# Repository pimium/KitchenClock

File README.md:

# KitchenClock
Kitchen Clock with an attiny13, oled display and two buttons.

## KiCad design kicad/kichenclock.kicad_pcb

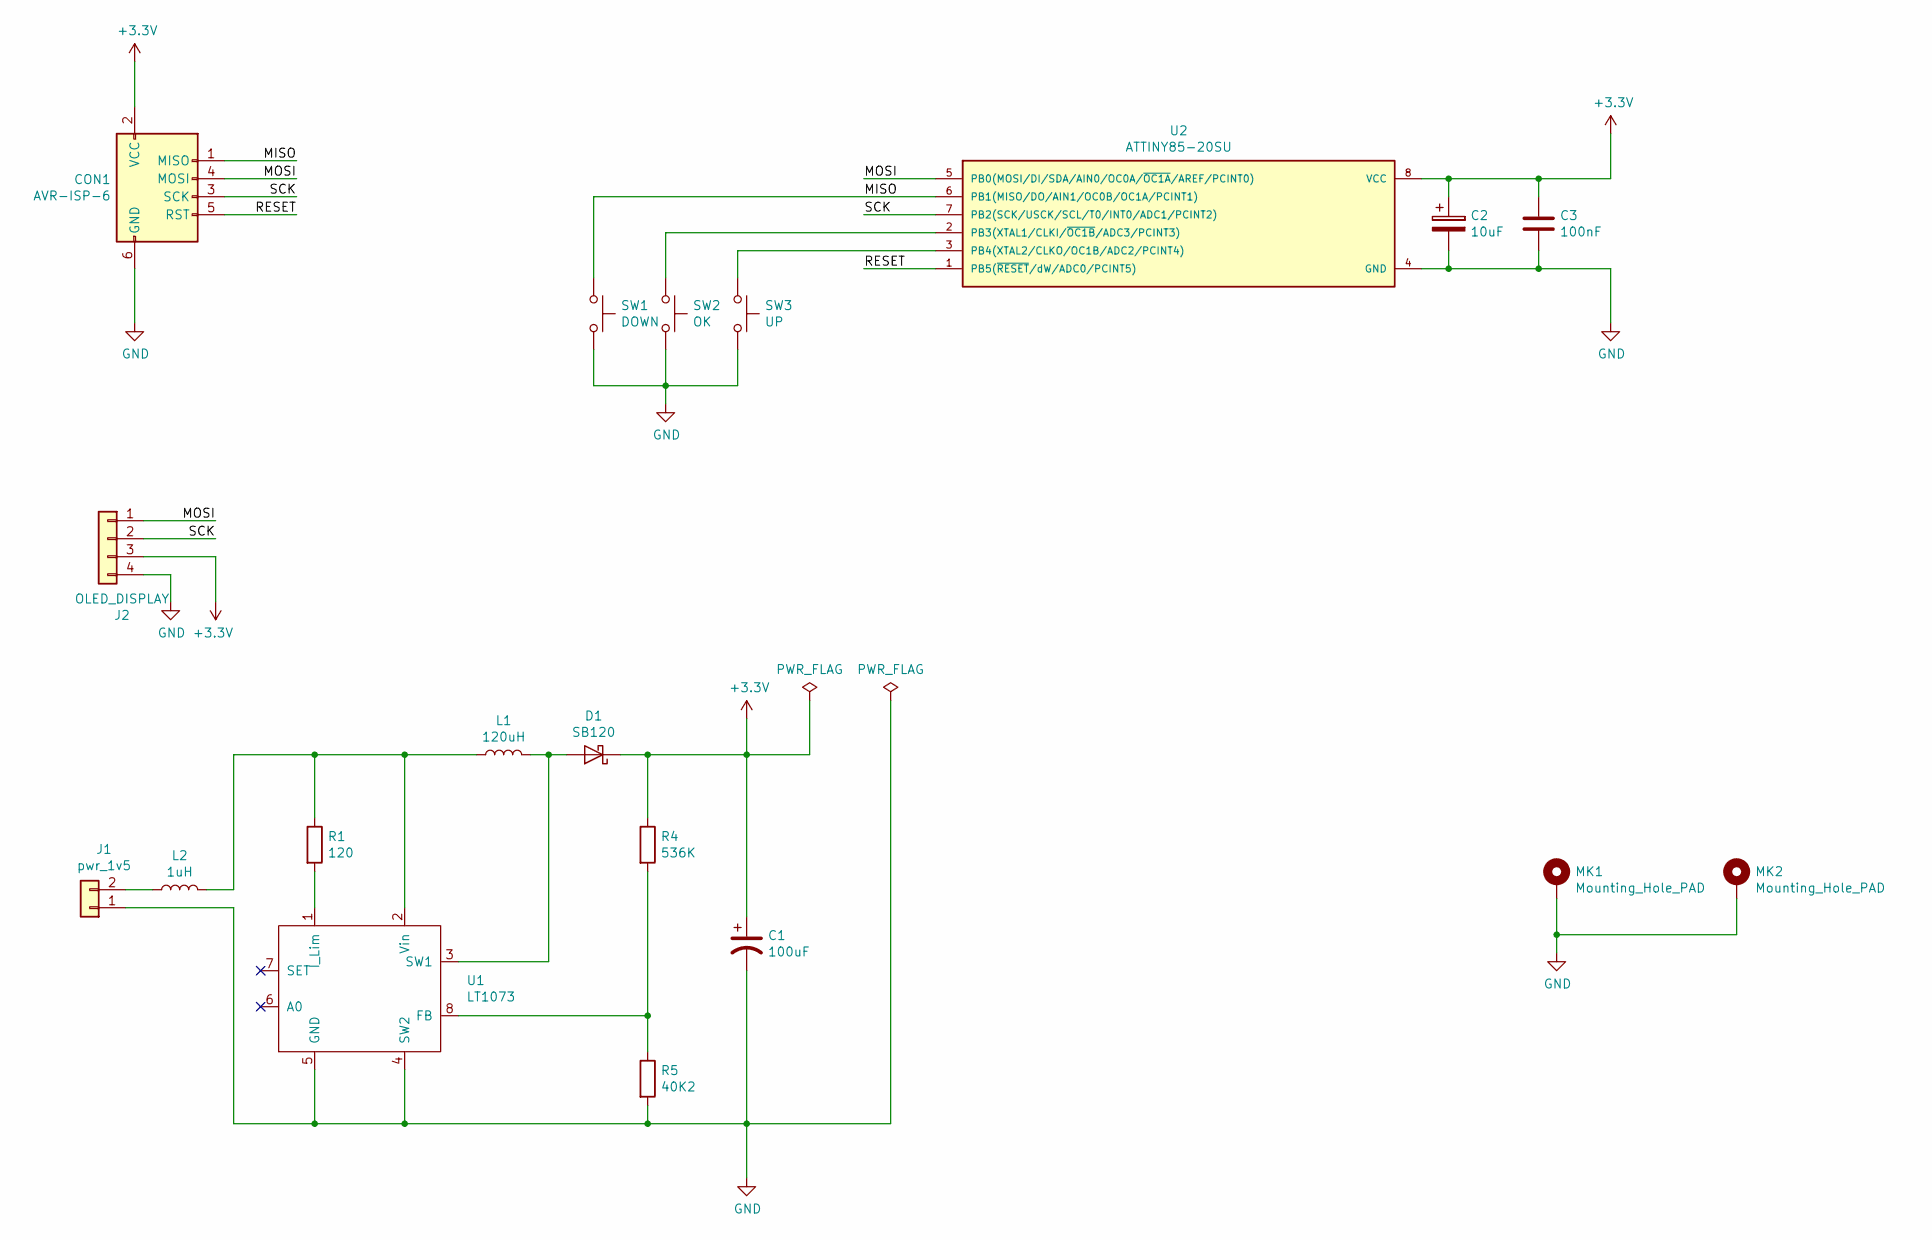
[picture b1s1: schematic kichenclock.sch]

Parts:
C1: 100uF; CP_EIA-6032-20_AVX-F_Pad2.24x2.40mm_HandSolder
C2: 10uF; CP_EIA-6032-20_AVX-F
C3: 100nF; C_0805_2012Metric_Pad1.15x1.50mm_HandSolder
CON1: AVR-ISP-6; PinSocket_2x03_P2.54mm_Vertical
D1: SB120; D_SMA_Handsoldering
J1: pwr_1v5; PinHeader_1x02_P2.54mm_Vertical
J2: OLED_DISPLAY; oled_128x32
L1: 120uH; Choke_CD75
L2: 1uH; L_0805_2012Metric_Pad1.15x1.50mm_HandSolder
MK1, MK2: Mounting_Hole_PAD; MountingHole_3mm_Pad
R1: 120; R_1206_3216Metric
R4: 536K; R_1206_3216Metric
R5: 40K2; R_1206_3216Metric
SW1: DOWN; SW_PUSH_6mm
SW2: OK; SW_PUSH_6mm
SW3: UP; SW_PUSH_6mm
U1: LT1073; SOIC-8_3.9x4.9mm_P1.27mm
U2: ATTINY85-20SU; SOIC-8_3.9x4.9mm_P1.27mm

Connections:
+3V3: C1.1, C2.1, C3.1, CON1.2 (VCC), D1.1 (K), J2.3, R4.1, U2.8 (VCC)
/MISO: CON1.1 (MISO), SW1.1, U2.6 (PB1(MISO/DO/AIN1/OC0B/OC1A/PCINT1))
/MOSI: CON1.4 (MOSI), J2.1, U2.5 (PB0(MOSI/DI/SDA/AIN0/OC0A/~OC1A~/AREF/P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)
/RESET: CON1.5 (RST), U2.1 (PB5(~RESET~/dW/ADC0/PCINT5))
/SCK: CON1.3 (SCK), J2.2, U2.7 (PB2(SCK/USCK/SCL/T0/INT0/ADC1/PCINT2))
GND: C1.2, C2.2, C3.2, CON1.6 (GND), J1.1, J2.4, MK1.1, MK2.1, R5.2, SW1.2, SW2.2, SW3.2, U1.4 (SW2), U1.5 (GND), U2.4 (GND)
unnamed: D1.2 (A), L1.2, U1.3 (SW1)
unnamed: J1.2, L2.1
unnamed: L1.1, L2.2, R1.1, U1.2 (Vin)
unnamed: R1.2, U1.1 (I_Lim)
unnamed: R4.2, R5.1, U1.8 (FB)
unnamed: SW2.1, U2.2 (PB3(XTAL1/CLKI/~OC1B~/ADC3/PCINT3))
unnamed: SW3.1, U2.3 (PB4(XTAL2/CLKO/OC1B/ADC2/PCINT4))

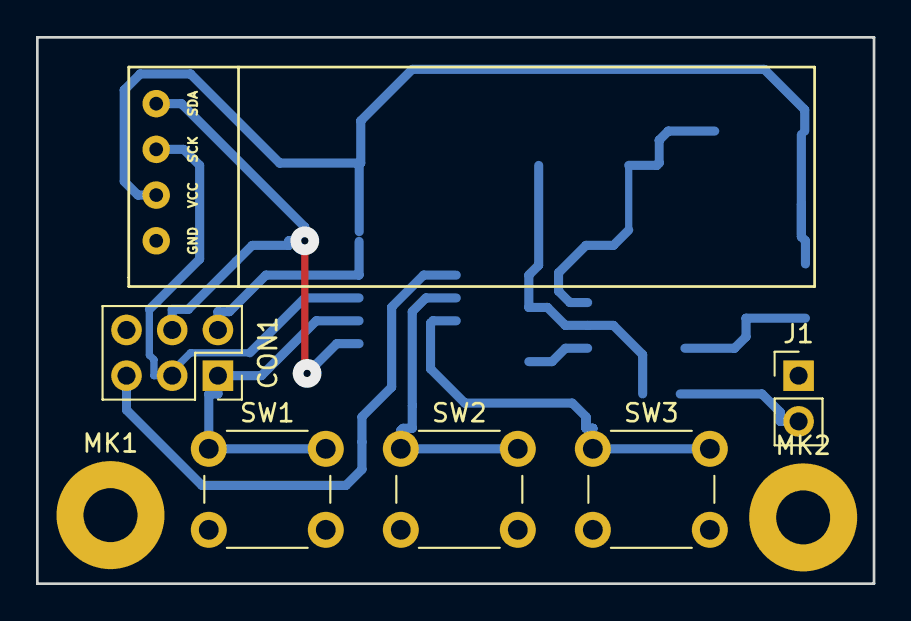
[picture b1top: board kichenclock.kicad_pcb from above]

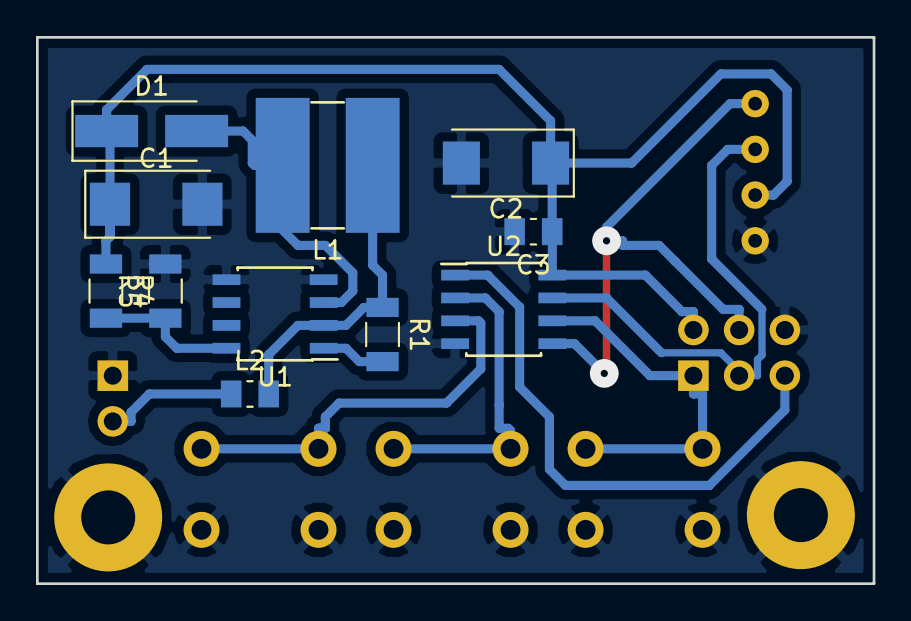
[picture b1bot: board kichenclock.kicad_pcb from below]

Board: 2 copper layers, 46.5 x 30.4 mm, 19 parts (11 on the bottom side), 13 nets.

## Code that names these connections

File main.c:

/**
 * SSD1306xLED - Drivers for SSD1306 controlled dot matrix OLED/PLED 128x64 displays
 *
 * @created: 2014-08-08
 * @author: Neven Boyanov
 *
 * This is part of the Tinusaur/SSD1306xLED project.
 *
 * Copyright (c) 2016 Neven Boyanov, Tinusaur Team. All Rights Reserved.
 * Distributed as open source software under MIT License, see LICENSE.txt file.
 * Please, as a favor, retain the link http://tinusaur.org to The Tinusaur Project.
 *
 * Source code available at: https://bitbucket.org/tinusaur/ssd1306xled
 *
 */

// ============================================================================

// #define F_CPU 1000000UL
// NOTE: The F_CPU (CPU frequency) should not be defined in the source code.
//       It should be defined in either (1) Makefile; or (2) in the IDE. 

#include <stdint.h>
#include <avr/io.h>
#include <util/delay.h>
#include <avr/interrupt.h>

//
// ~~~~~~~~~~~~~~~~~~~~~~~~~~~~~~~~~~~~~~
//                ATtiny
//               25/45/85
//              +----------+   (-)-------
//      (RST)---+ PB5  Vcc +---(+)-------
// --[OWOWOD]---+ PB3  PB2 +---[TWI/SCL]-
//           ---+ PB4  PB1 +---
// -------(-)---+ GND  PB0 +---[TWI/SDA]-
//              +----------+
//
// ~~~~~~~~~~~~~~~~~~~~~~~~~~~~~~~~~~~~~~

// -----(+)--------------->	// Vcc,	Pin 1 on SSD1306 Board
// -----(-)--------------->	// GND,	Pin 2 on SSD1306 Board
#define SSD1306_SCL        PB2    // SCL,	Pin 3 on SSD1306 Board
#define SSD1306_SDA        PB0    // SDA,	Pin 4 on SSD1306 Board

#define SSD1306_SA        0x78    // Slave address

// ----------------------------------------------------------------------------

#include "ssd1306xled.h"
//#include "print_3x7.h"
#include "print_5x7.h"
#include "print_10x14.h"
#include "num2str.h"
//#include "cpufreq.h"

// ----------------------------------------------------------------------------

#define IDLE 0
#define ARMED 1
#define COUNTING 2
#define WAIT 3

#include <util/delay.h>

volatile uint8_t sec = 50, display_time = 1;
uint8_t display_date = 1, days = 8, month = 4;
uint16_t year = 2018;
volatile uint8_t hour = 23, min = 59;
volatile uint16_t counter_interrupt = 0;
volatile uint8_t state = IDLE;
// ----------------------------------------------------------------------------

static char daytab[2][13] =
        {
                {0, 31, 28, 31, 30, 31, 30, 31, 31, 30, 31, 30, 31},
                {0, 31, 29, 31, 30, 31, 30, 31, 31, 30, 31, 30, 31}
        };

static char weekdaytab[7][3] =
        {
                {'M', 'O', 0},
                {'D', 'I', 0},
                {'M', 'I', 0},
                {'D', 'O', 0},
                {'F', 'R', 0},
                {'S', 'A', 0},
                {'S', 'O', 0}
        };

char ssd1306_numdec_buffer[USINT2DECASCII_MAX_DIGITS + 1];

#if 1

ISR(PCINT0_vect) {
//    switch (state) {
//        case ARMED:
//
//            TCNT1 = 0;
//            TCCR1 |= (1 << CS12) | (1 << CS12);
//            state = COUNTING;
//            break;
//
//        case COUNTING:
//            counter = TCNT1;
//            TCCR1 &= ~((1 << CS13) | (1 << CS12) | (1 << CS11) | (1 << CS10));
//            state = WAIT;
//            break;
//        default:;
//    }
}

ISR(TIMER1_OVF_vect) {
    if (counter_interrupt == 15625) {
        counter_interrupt = 0;
        sec++;
        if (sec == 60) {
            min++;
            sec = 0;
            if (min == 60) {
                hour++;
                min = 0;
                if(hour == 24) {
                    hour = 0;
                    display_date = 1;
                    days++;
                }
            }
        }
        display_time = 1;
    }
    counter_interrupt++;
}


static inline void initTimer1(void) {
//    TCCR1 |= (0 << CTC1);  // clear timer on compare match
    TCCR1 |= (0 << CS13) | (0 << CS12) | (1 << CS11) | (0 << CS10);
    OCR1C = 0xff; // compare match value
    TIMSK |= (1 << TOIE1); // enable overflow interrupt
}

#endif

static inline void init_PCINT_Interrupt(void) {
    GIMSK |= (1 << PCIE);   // pin change interrupt enable
    PCMSK |= (1 << PCINT4); // pin change interrupt enabled for PCINT4
    sei();                  // enable interrupts
}

uint8_t is_leap_year(uint16_t year){
    uint8_t leap;
    if (year%4 == 0)
        leap = 1;
    else
        leap = 0;
    if (year%100 == 0 && year%400 != 0)
        leap = 0;
    return leap;
}

// https://en.wikipedia.org/wiki/Determination_of_the_day_of_the_week
uint8_t daystotal (uint16_t y, uint8_t m, uint8_t d)
{
    uint16_t daystotal = d;
    for (int year = 1 ; year <= y ; year++)
    {
        int max_month = ( year < y ? 12 : m-1 );
        int leap = is_leap_year(year);
        for (int month = 1 ; month <= max_month ; month++)
        {
            daystotal += daytab[leap][month];
        }
    }
    return (uint8_t) (daystotal%7);
}

int main(void) {
    uint8_t week_days = daystotal(year, month, days);

    ssd1306_numdec_buffer[USINT2DECASCII_MAX_DIGITS] = '\0';   // Terminate the string.
    // ---- Initialization ----

    // Small delay is necessary if ssd1306_init is the first operation in the application.
    _delay_ms(40);
    ssd1306_oled *f10x14 = font10x14_init();
    _delay_ms(40);
    ssd1306_oled *f5x7 = font5x7_init();

    f5x7->ssd1306_init();
    f5x7->ssd1306_clear();

    _delay_ms(100);

    DDRB |= (1 << PB3);
    init_PCINT_Interrupt();
    initTimer1();
    sei();



//    f10x14->put_char(0,3,'I');
//    f10x14->put_char(12,3,'A');
//    f10x14->put_char(24,3,'C');
//    f10x14->put_char(38,3,'8');

    // ---- Main Loop ----

#if 1
    for (;;) {
        if(display_date){
//            days++;
            if(days == daytab[is_leap_year(year)][month]){
                days = 0;
                month++;
                if(month == 13){
                    month = 1;
                    year++;
                }

            }

//            usint2decascii(, ssd1306_numdec_buffer);
            f5x7->put_string(30, 0, weekdaytab[(week_days++)%7]);

            usint2decascii(days, ssd1306_numdec_buffer);

            f5x7->put_string(50, 0, ssd1306_numdec_buffer);
            f5x7->put_char(62, 0, '.');

            usint2decascii(month, ssd1306_numdec_buffer);
            f5x7->put_string(68, 0, ssd1306_numdec_buffer);
            f5x7->put_char(80, 0, '.');

            usint2decascii(year%100, ssd1306_numdec_buffer);
            f5x7->put_string(86, 0, ssd1306_numdec_buffer);

            display_date = 0;
        }

        if (display_time) {
            f10x14->put_char(44, 4, ' ');
            f10x14->put_char(80, 4, ' ');
            usint2decascii(hour, ssd1306_numdec_buffer);
            f10x14->put_string(20, 4, ssd1306_numdec_buffer);
            usint2decascii(min, ssd1306_numdec_buffer);
            f10x14->put_string(56, 4, ssd1306_numdec_buffer);
            usint2decascii(sec, ssd1306_numdec_buffer);
            f10x14->put_string(92, 4, ssd1306_numdec_buffer);
            f10x14->put_char(44, 4, ':');
            f10x14->put_char(80, 4, ':');
            display_time = 0;
        }
    }
#endif

    return 0;
}

// ============================================================================

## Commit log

2018-04-08 The attiny13 has a very small flash. We use the attiny85 now
2018-04-08 Clock display is working rudimentar but working to settings with push buttons
2018-04-09 move firmware to avr folder
2018-04-09 add kicad files
2018-04-11 board done
2018-04-11 kicad files done
2018-04-29 change the most path to 20 mil
